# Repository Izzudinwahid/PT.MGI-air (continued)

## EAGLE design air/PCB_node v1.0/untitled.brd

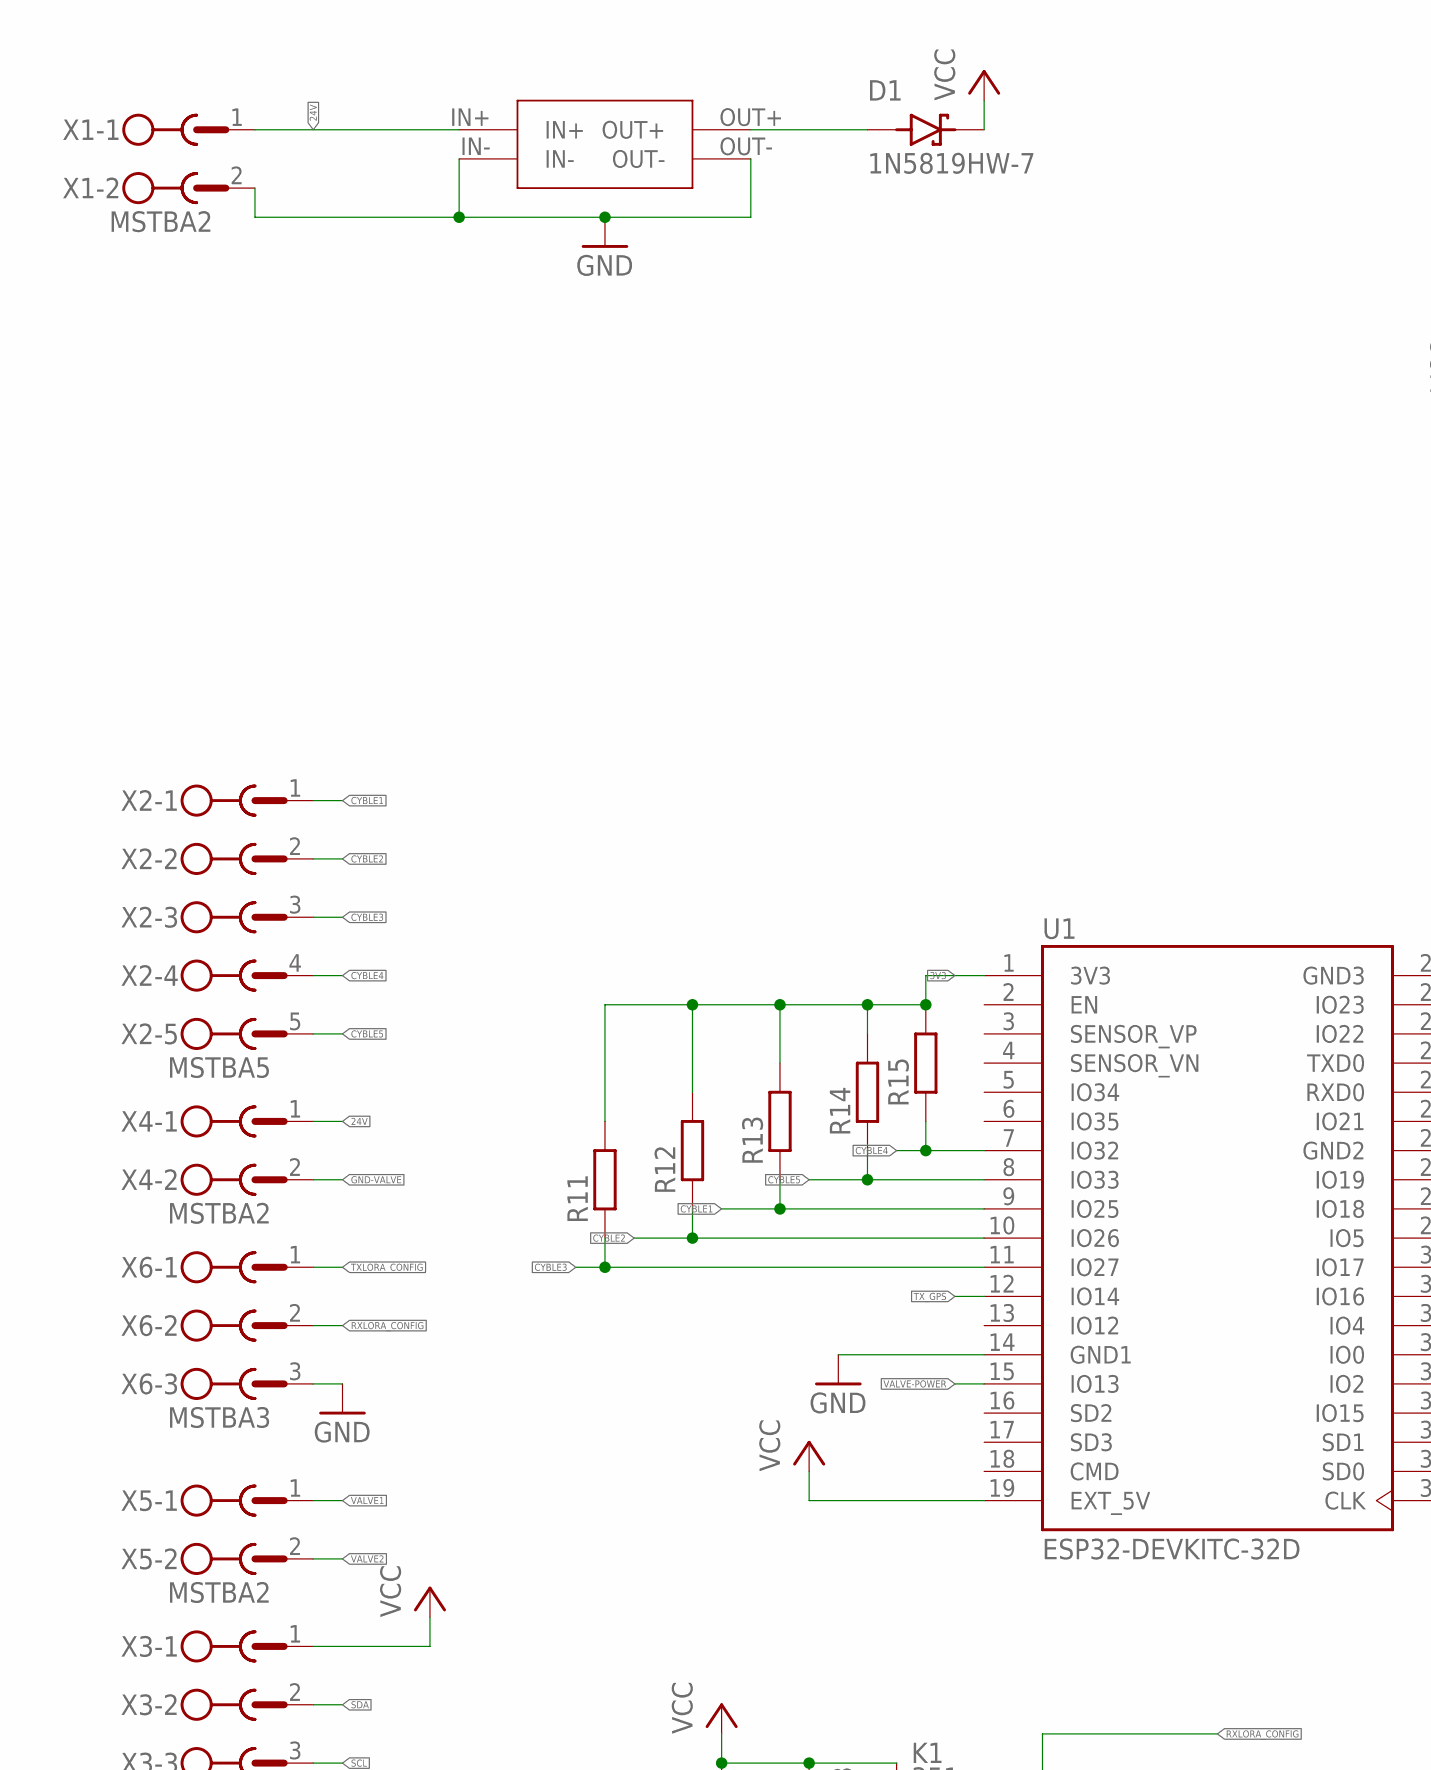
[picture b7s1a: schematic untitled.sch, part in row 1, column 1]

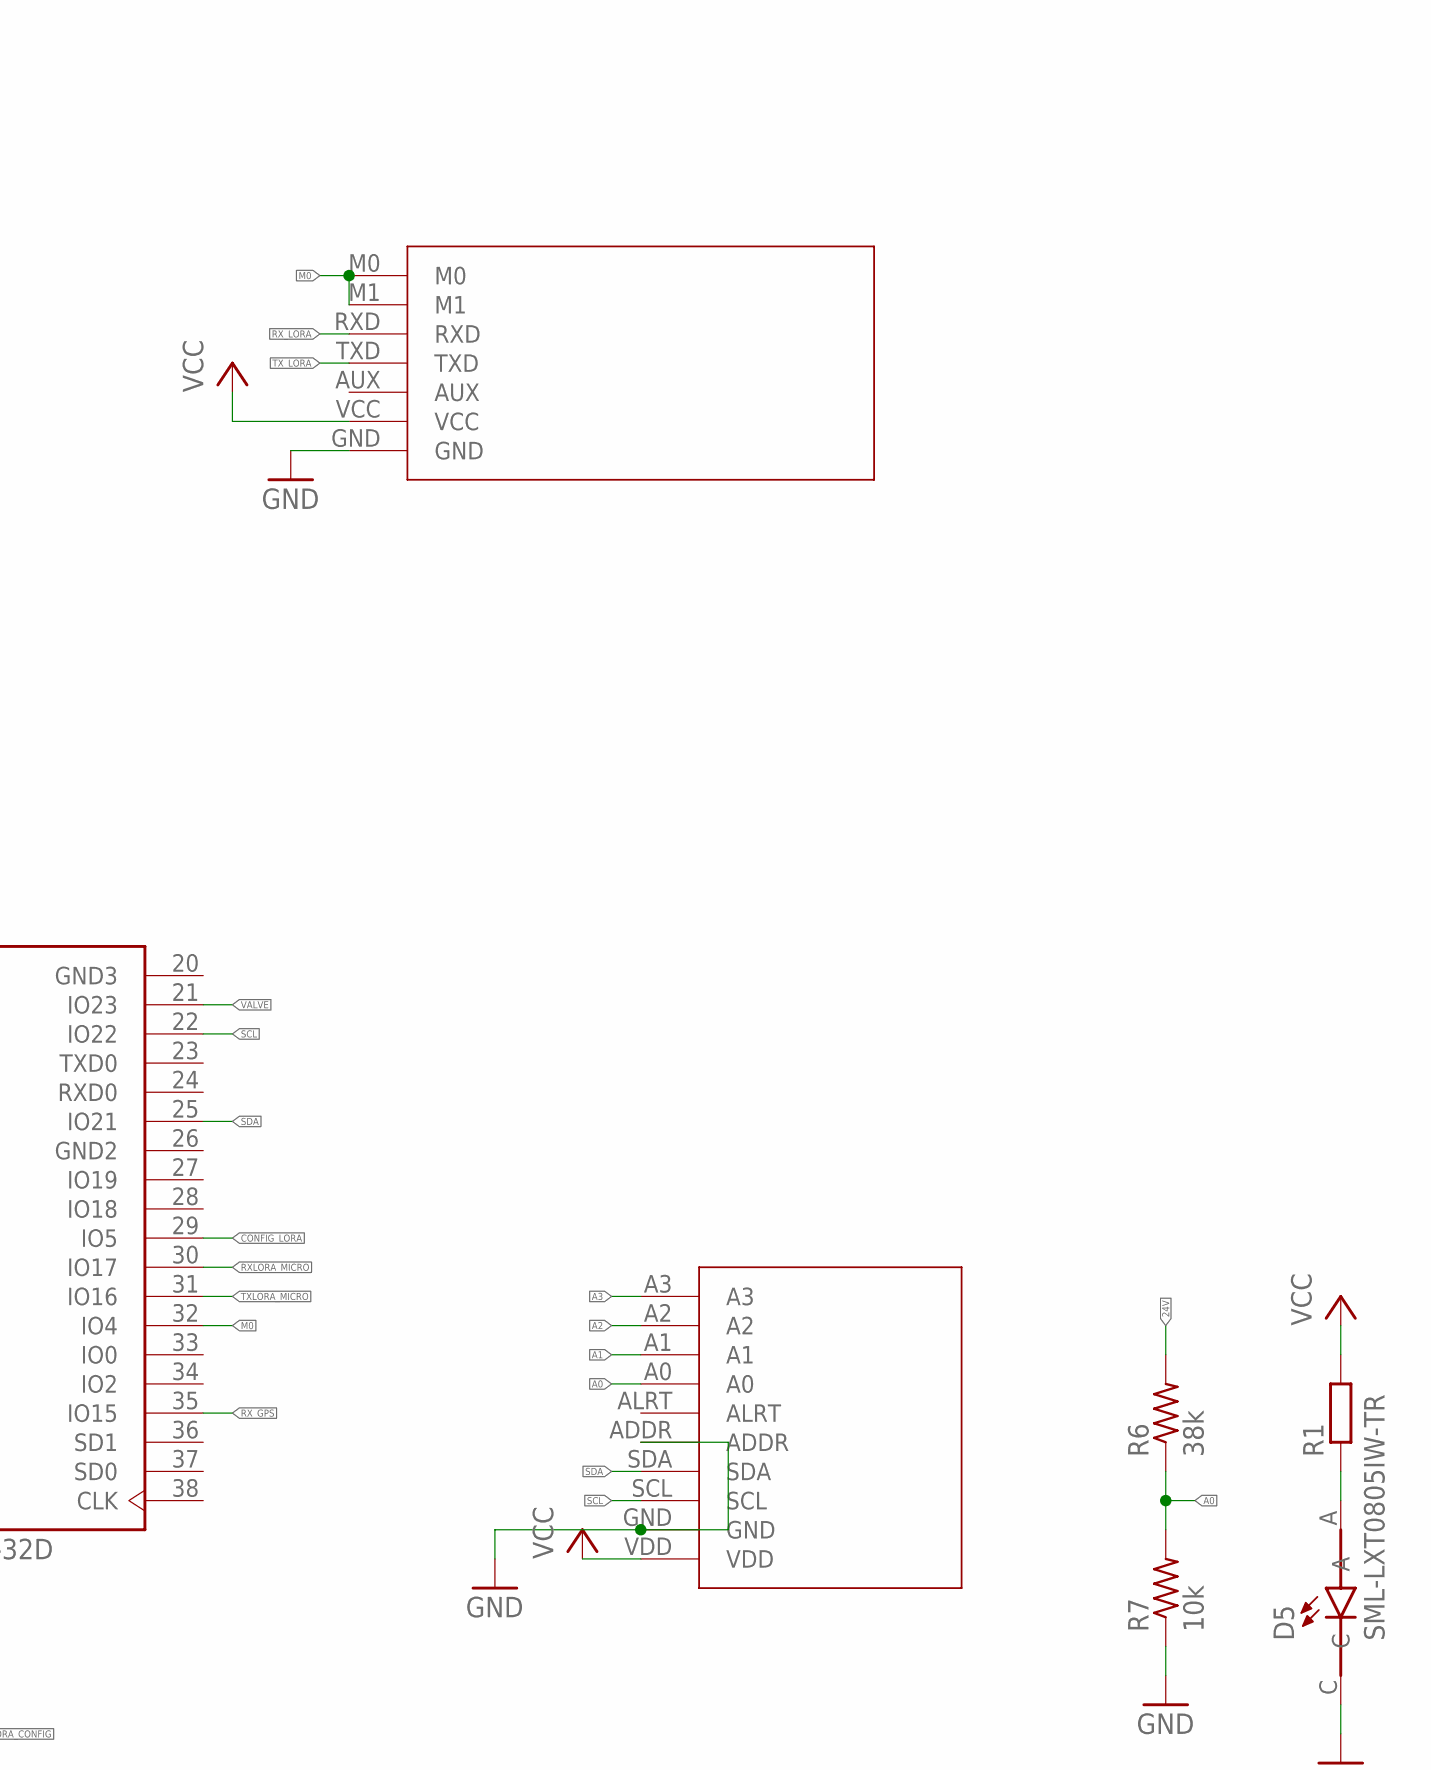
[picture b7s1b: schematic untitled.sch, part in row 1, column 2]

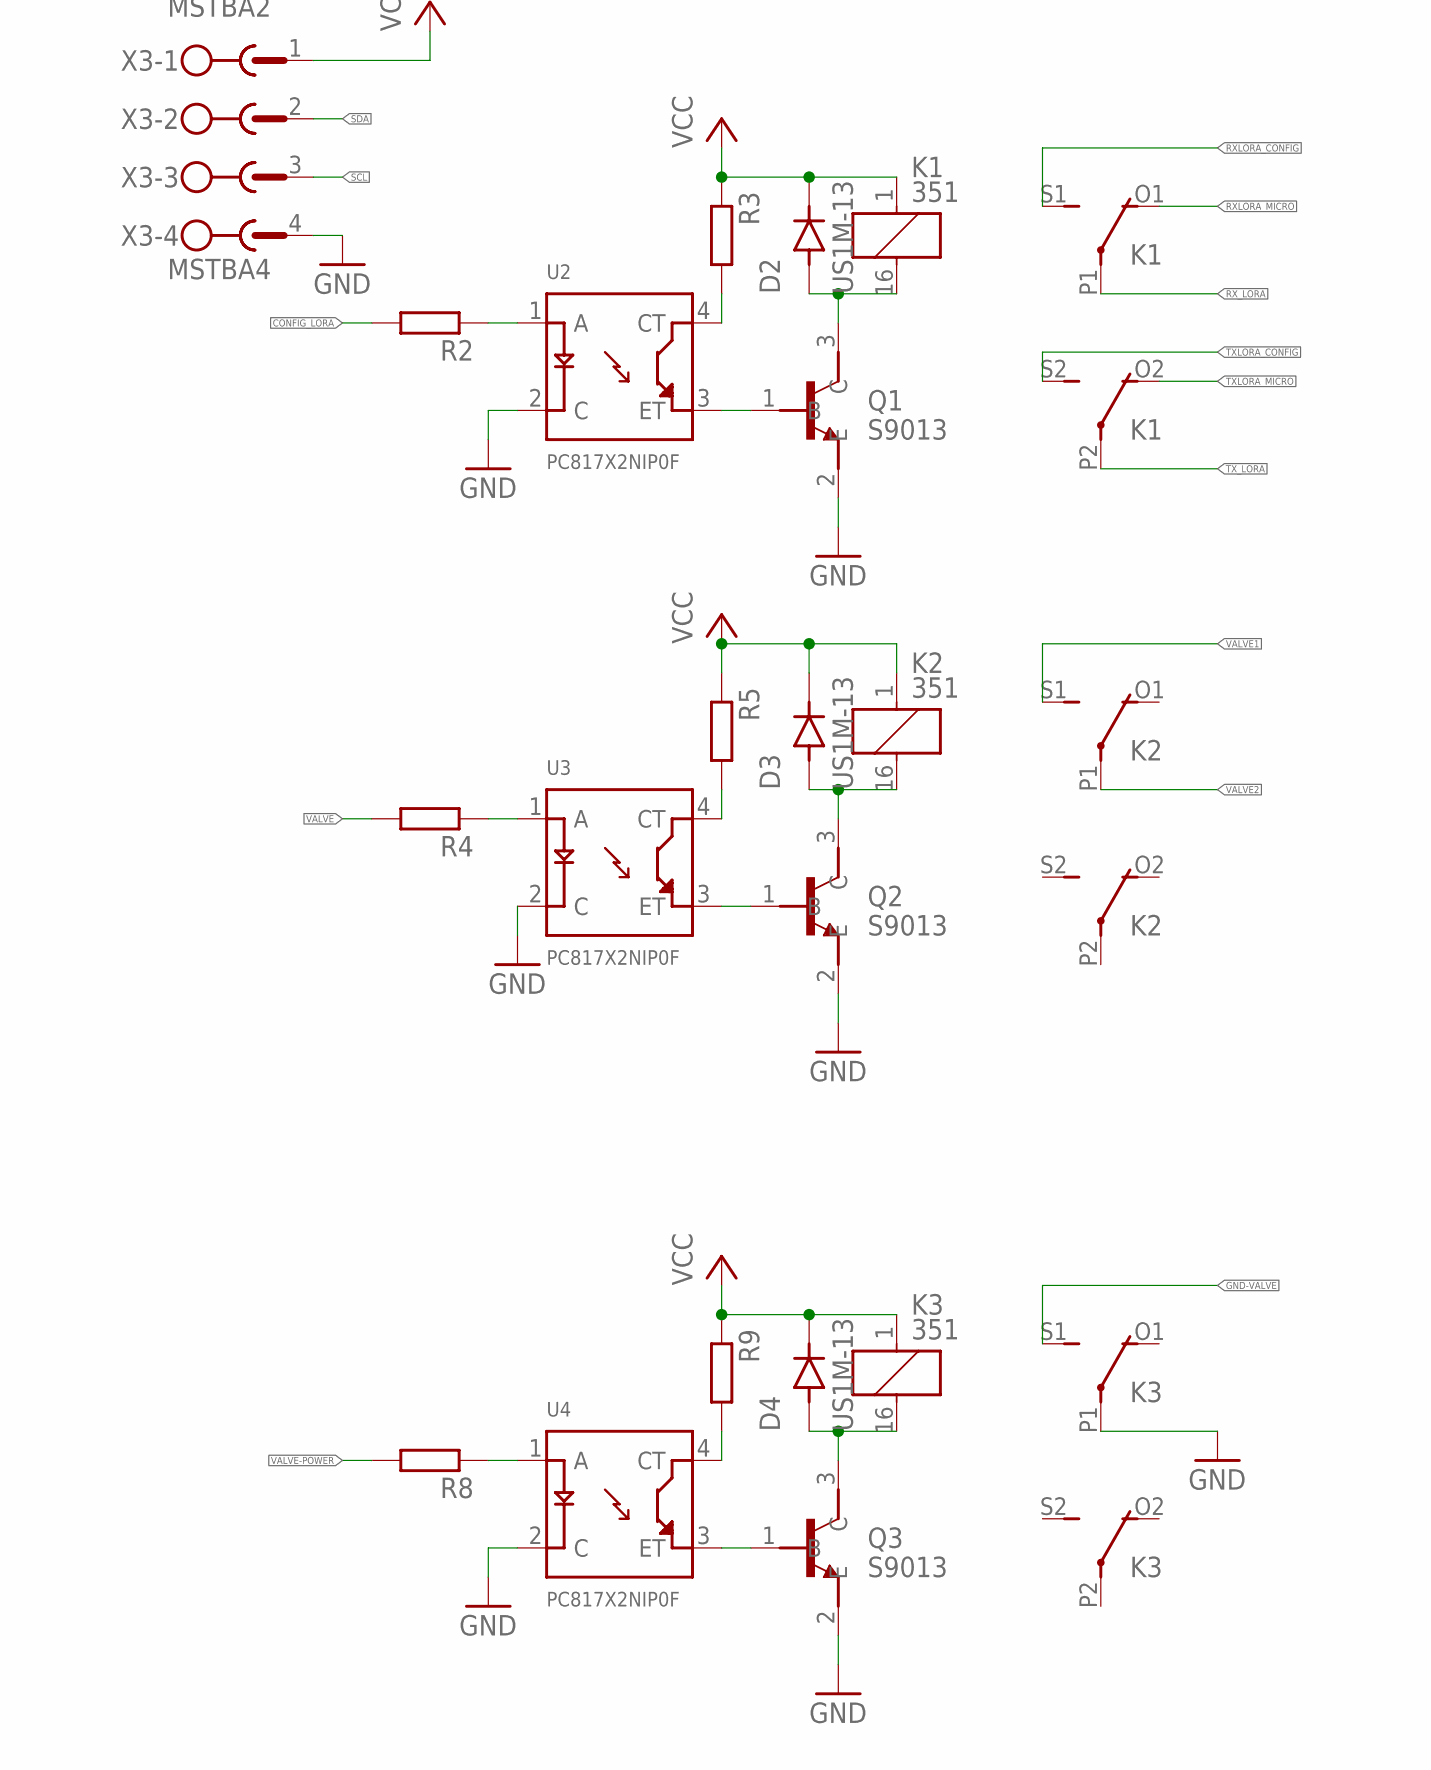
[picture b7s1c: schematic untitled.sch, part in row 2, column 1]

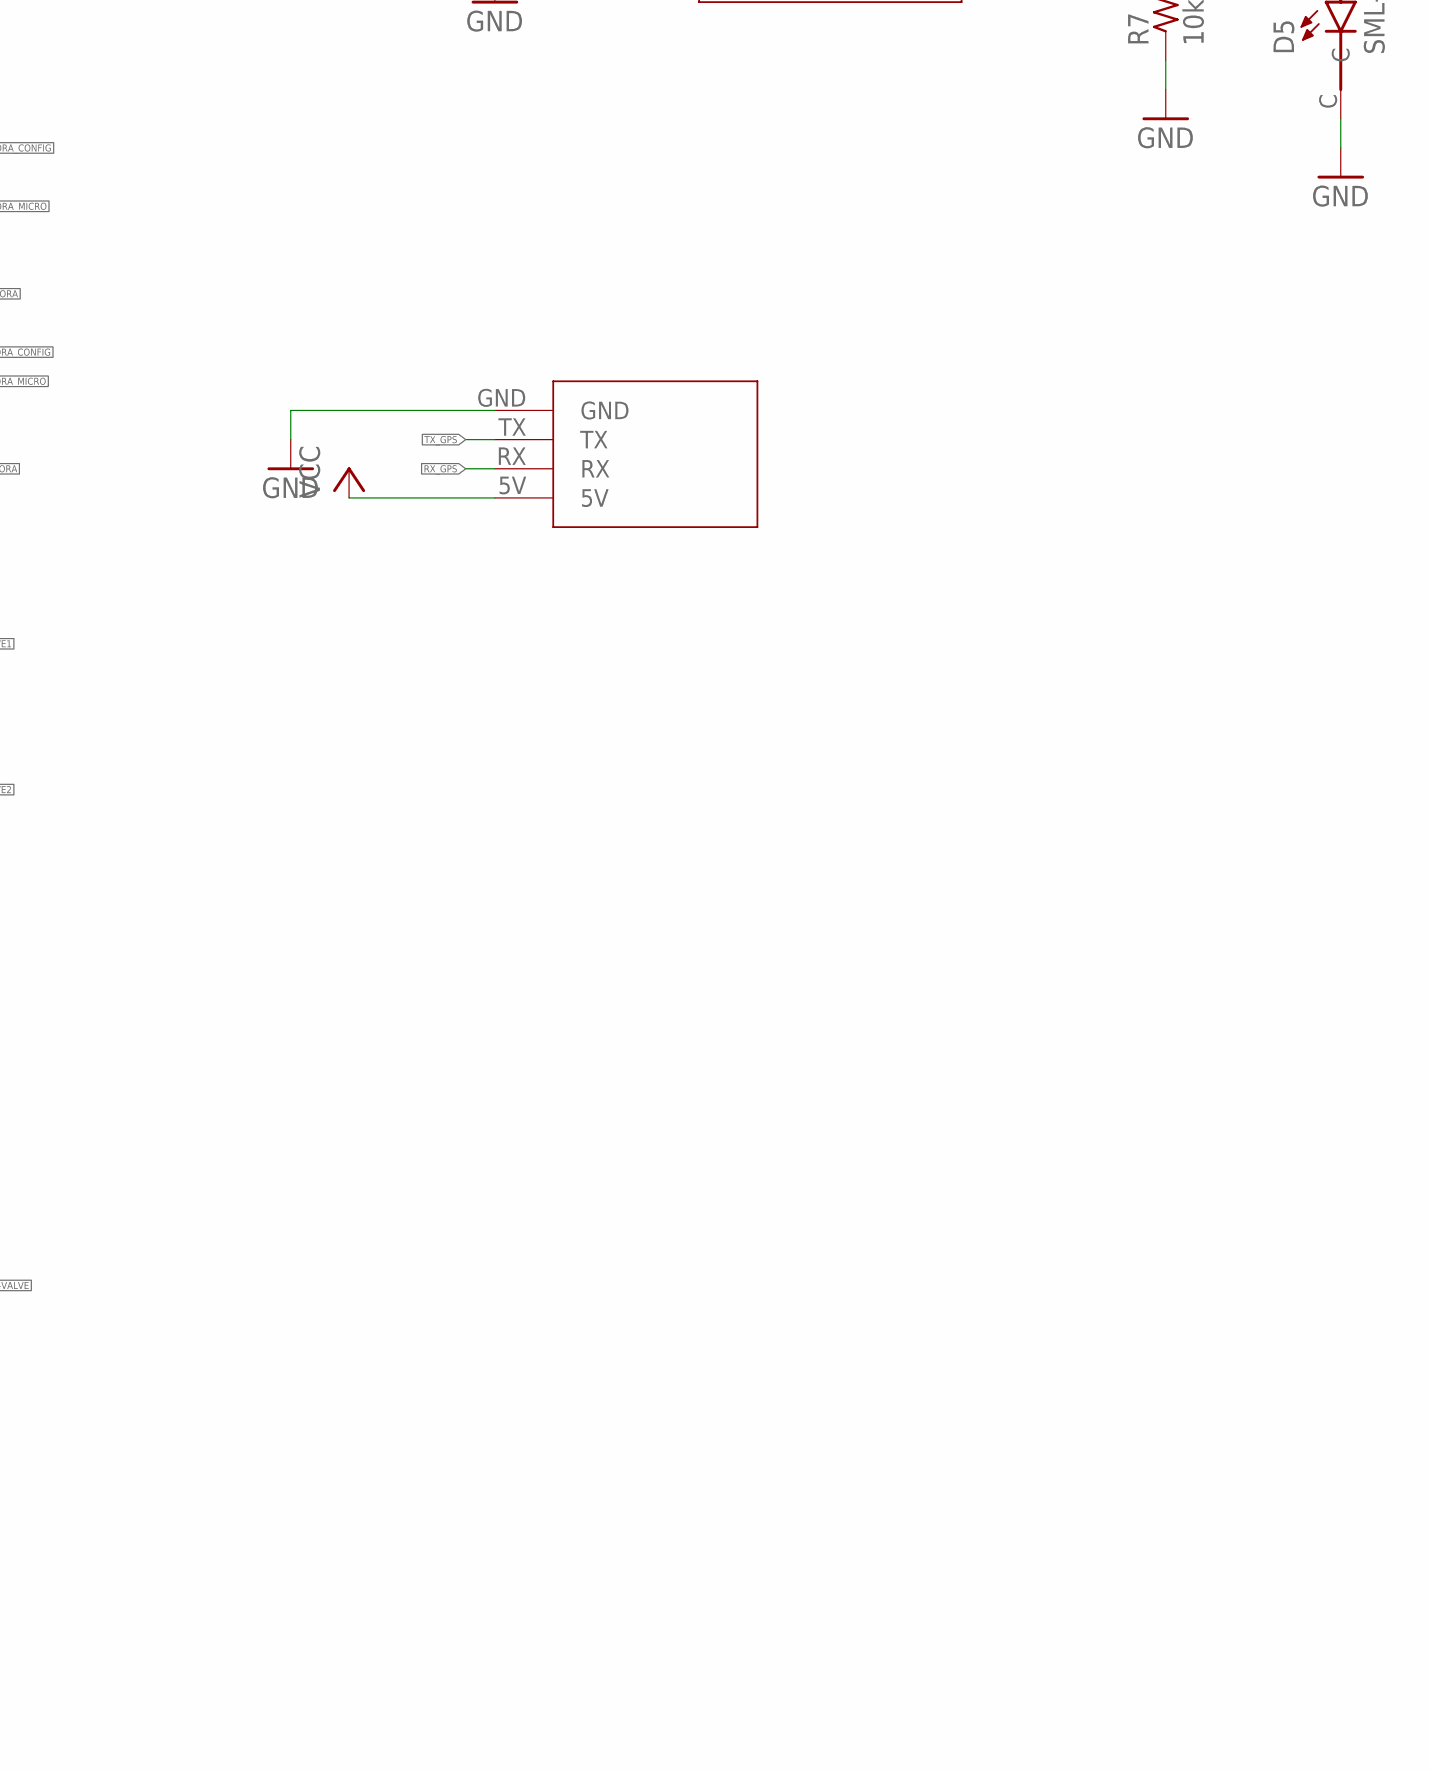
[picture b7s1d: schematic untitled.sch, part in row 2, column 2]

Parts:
ADS1: ADS1115
D1: 1N5819HW-7; SOD3715X145N
D2, D3, D4: US1M-13; DIOM5226X240N
D5: SML-LXT0805IW-TR; LEDC2012X120N
EBYTEE220-900T22D1: EBYTEE220-900T22D
K1, K2, K3: 351
MINI1: MINI560
NEO-6MGPS1: NEO-6MGPS
Q1, Q2, Q3: S9013; SOT95P240X120-3N
R1, R2, R3, R4, R5, R8, R9, R11, R12, R13, R14, R15: R-EU_R0805; R0805
R6: 38k; 0207/12
R7: 10k; 0207/12
U1: ESP32-DEVKITC-32D; MODULE_ESP32-DEVKITC-32D
U2, U3, U4: PC817X2NIP0F; SOT254P975X400-4N
X1, X4, X5: MSTBA2
X2: MSTBA5
X3: MSTBA4
X6: MSTBA3

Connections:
3V3: R11.2, R12.2, R13.2, R14.2, R15.2, U1.1 (3V3)
24V: MINI1.IN+, R6.2, X1.1, X4.1
A0: ADS1.A0, R6.1, R7.2
A1: ADS1.A1
A2: ADS1.A2
A3: ADS1.A3
CONFIG_LORA: R2.2, U1.29 (IO5)
CYBLE1: R13.1, U1.9 (IO25), X2.1
CYBLE2: R12.1, U1.10 (IO26), X2.2
CYBLE3: R11.1, U1.11 (IO27), X2.3
CYBLE4: R15.1, U1.7 (IO32), X2.4
CYBLE5: R14.1, U1.8 (IO33), X2.5
GND: ADS1.ADDR, ADS1.GND, D5.C, EBYTEE220-900T22D1.GND, K3.P1, MINI1.IN-, MINI1.OUT-, NEO-6MGPS1.GND, Q1.2 (E), Q2.2 (E), Q3.2 (E), R7.1, U1.14 (GND1), U2.2 (C), U3.2 (C), U4.2 (C), X1.2, X3.4, X6.3
GND2: U1.26 (GND2)
GND3: U1.20 (GND3)
GND-VALVE: K3.S1 (S), X4.2
M0: EBYTEE220-900T22D1.M0, EBYTEE220-900T22D1.M1, U1.32 (IO4)
unnamed: D5.A, R1.1
unnamed: R2.1, U2.1 (A)
unnamed: D1.A, MINI1.OUT+
unnamed: R8.1, U4.1 (A)
unnamed: R3.2, U2.4 (CT)
unnamed: D2.A, K1.16 (2), Q1.3 (C)
unnamed: Q1.1 (B), U2.3 (ET)
unnamed: R9.2, U4.4 (CT)
unnamed: R4.1, U3.1 (A)
unnamed: Q2.1 (B), U3.3 (ET)
unnamed: Q3.1 (B), U4.3 (ET)
unnamed: R5.2, U3.4 (CT)
unnamed: D4.A, K3.16 (2), Q3.3 (C)
unnamed: D3.A, K2.16 (2), Q2.3 (C)
RXLORA_CONFIG: K1.S1 (S), X6.2
RXLORA_MICRO: K1.O1 (O), U1.30 (IO17)
RX_GPS: NEO-6MGPS1.RX, U1.35 (IO15)
RX_LORA: EBYTEE220-900T22D1.RXD, K1.P1
SCL: ADS1.SCL, U1.22 (IO22), X3.3
SDA: ADS1.SDA, U1.25 (IO21), X3.2
TXLORA_CONFIG: K1.S2 (S), X6.1
TXLORA_MICRO: K1.O2 (O), U1.31 (IO16)
TX_GPS: NEO-6MGPS1.TX, U1.12 (IO14)
TX_LORA: EBYTEE220-900T22D1.TXD, K1.P2
VALVE: R4.2, U1.21 (IO23)
VALVE1: K2.S1 (S), X5.1
VALVE2: K2.P1, X5.2
VALVE-POWER: R8.2, U1.15 (IO13)
VCC: ADS1.VDD, D1.C (K), D2.C (K), D3.C (K), D4.C (K), EBYTEE220-900T22D1.VCC, K1.1, K2.1, K3.1, NEO-6MGPS1.5V, R1.2, R3.1, R5.1, R9.1, U1.19 (EXT_5V), X3.1

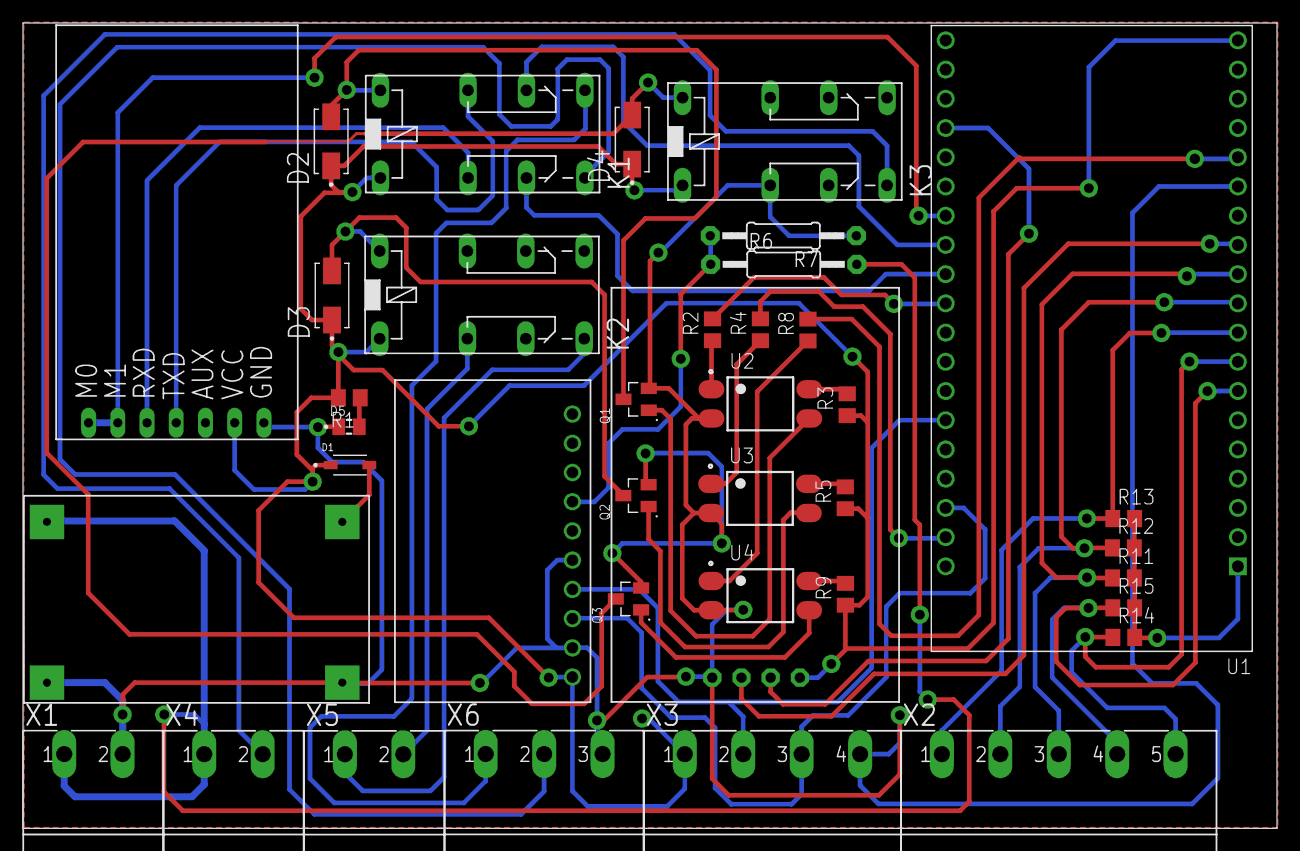
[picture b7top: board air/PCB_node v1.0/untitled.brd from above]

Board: 2 copper layers, 109.0 x 70.0 mm, 39 parts (0 on the bottom side), 41 nets.

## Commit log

2023-02-22 PCB air
2023-02-23 revisi PCB dan List komponen
2023-02-24 revisi tanggal 24/02/2023
2023-03-03 menmbahkan pcb tambahan
2023-03-27 PCB dasWater v1.1
2023-03-30 PCB dasmeter dengan multidop
2023-03-30 desain PCB scada air
2023-04-06 revisi multidrop
2023-04-11 revisi scada air
2023-04-17 menambah GPS chip
2023-05-31 fix PCB
2023-06-09 PCB fix dasmeter
2023-06-21 fix PCB gateway box lama
2023-12-07 scada air
2023-12-07 revisi BoM scada air
2023-12-07 revisi dioda schotky
2023-12-28 PCB scada air V2
